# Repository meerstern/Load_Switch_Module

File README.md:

# Load_Switch_Module
SiP32431 load switch module 

## 概要 
  * Vishay製超低漏洩電流ロードスイッチ[SiP32431][1]を搭載した変換基板です。
  * 1.5V~5.5V、最⼤1.4Aまでの負荷の電源管理が可能です。  
  * SDカードやセンサ等をマイコンからON/OFF制御する場合に最適です。
  * FETを使⽤する場合に⽐べ、漏れ電流が10pAと非常に⼩さいことが特徴です。
  * EN端⼦がHighの時、VOUTからVIN電源が出⼒されます。  
  * 安定化のため、EN端子は基板上で20kΩでプルダウンしています。  
  * 電池で駆動させるIoT機器ではロードスイッチは欠かせません。  
  
## 販売サイト
  * [スイッチサイエンス][2]

[1]: https://www.vishay.com/docs/66597/sip32431.pdf "*1"
[2]: https://www.switch-science.com/products/5796
MIT Lisense

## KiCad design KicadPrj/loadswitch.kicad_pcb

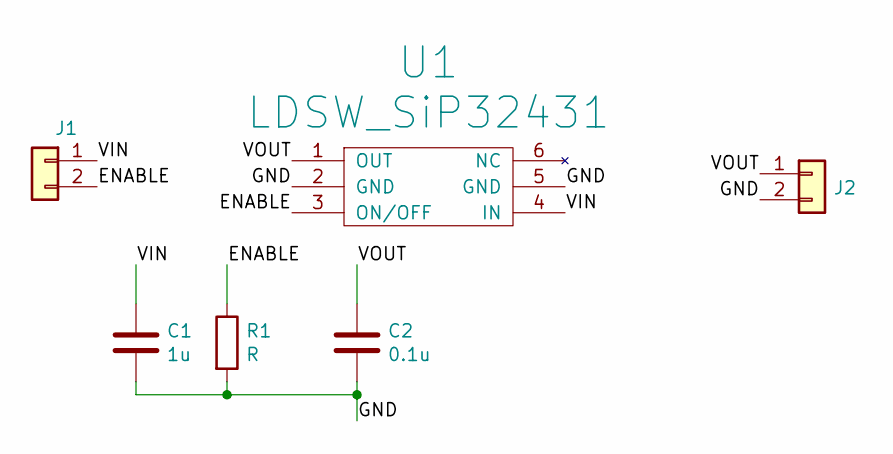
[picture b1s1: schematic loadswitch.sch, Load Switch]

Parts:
C1: 1u; C_0603_1608Metric
C2: 0.1u; C_0603_1608Metric
J1, J2: Conn_01x02; PinHeader_1x02_P2.54mm_Vertical
R1: R; R_0603_1608Metric
U1: LDSW_SiP32431; SOT-363_SC-70-6

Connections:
/ENABLE: J1.2, R1.1, U1.3 (ON/OFF)
/GND: C1.2, C2.2, J2.2, R1.2, U1.2 (GND), U1.5 (GND)
/VIN: C1.1, J1.1, U1.4 (IN)
/VOUT: C2.1, J2.1, U1.1 (OUT)

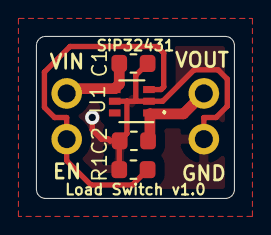
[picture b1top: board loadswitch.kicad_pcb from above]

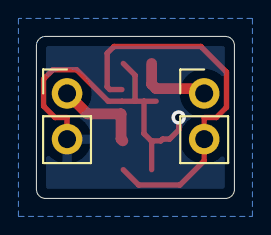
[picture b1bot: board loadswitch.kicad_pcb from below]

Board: 2 copper layers, 11.0 x 9.0 mm, 6 parts (2 on the bottom side), 4 nets.

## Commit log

2019-06-28 Upload the kicad project
2019-07-03 Add imeges
2022-12-06 Add shop link
